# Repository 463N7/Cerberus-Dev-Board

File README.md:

# Cerberus Dev Board

The hardware and programming reference for the Cerberus handheld development board: ESP32-S3 + ESP32-C5, ST7796 display, GT911 touch, microSD, battery monitoring, and expansion interfaces.

**[Open the developer website](https://463n7.github.io/Cerberus-Dev-Board/)** · **[USB firmware installer](https://463n7.github.io/Cerberus-Flasher/)**

This repository documents the device itself, independently of a particular firmware application. **No Cerberus main-device schematics, PCB sources, fabrication files, or netlists are included.** Expansion files have a separate, clearly marked home under [`hardware/expansion/`](hardware/expansion/README.md). The supplied expansion starter includes its connector-only schematic.

**[Expansion starter KiCad project](hardware/expansion/starter/)** · **[Download starter ZIP](https://463n7.github.io/Cerberus-Dev-Board/assets/cerberus-expansion-starter.zip)** — KiCad 10 project, PCB, and expansion connector schematic.

## Developer reference

| Guide | Contents |
| --- | --- |
| [Start here](content/getting-started.md) | Identify the board, install firmware, build, and recover USB |
| [Hardware](content/hardware.md) | Base-board processors, memory, buses, and power devices |
| [Pinouts](content/pinouts.md) | Base-board interfaces, labeled expansion breakout, and six-C5 expansion pinout; RF/NFC map not published during early testing |
| [Expansion add-ons](content/expansion.md) | Six-C5 bank and RF/NFC board; both in testing |
| [Programming](content/programming.md) | Toolchain, source layout, memory setup, protocol, and bring-up |
| [Batteries](content/batteries.md) | Tested batteries, “should fit” candidates, dimensions, polarity, and test evidence |
| [Antennas](content/antennas.md) | Radio-specific antenna requirements, connector checks, and comparison records |
| [Troubleshooting](content/troubleshooting.md) | USB, C5, display, touch, SD, battery, and expansion issues |
| [Downloads](content/downloads.md) | Firmware, reusable pin definitions, examples, and expansion CAD location |
| [Reference and testing](content/revisions.md) | Base-board reference, add-on testing status, and remaining measurements |

Cerberus uses an **S3 N16R2, one onboard C5, and 1-bit SDMMC with a 40 MHz maximum target**. The C5 memory specification uses the smallest standard [C5-WROOM option](https://documentation.espressif.com/esp32-c5-wroom-1_wroom-1u_datasheet_en.html): **N4, 4 MB flash and no PSRAM**. Sentinel's current 2 MB firmware layout is a separate software allocation. The RF/NFC board and six-C5 bank are optional expansion add-ons, both in testing. The expansion breakout table lists all 25 GPIO signals individually, with each processor and side identified as viewed from the labeled face.

## Maintaining the website

Edit the Markdown in `content/`, then generate the static website:

```powershell
python -m pip install -r requirements.txt
python tools/build_site.py
python tools/check_site.py
python -m http.server 8765 --directory docs
```

Open `http://localhost:8765/`. Commit both the Markdown sources and generated `docs/`. GitHub Pages serves `main:/docs`. The repository check verifies generated content, local links, and the boundary excluding main-device design files.

## Compatibility reports

Use the [battery, antenna, or documentation issue templates](https://github.com/463N7/Cerberus-Dev-Board/issues/new/choose). Include exact model numbers, board revision, measurements, test conditions, and photographs that do not reveal device schematics. “Should fit” is a dimensional estimate, not a tested battery recommendation.

No general hardware license is granted by publishing this reference. Expansion CAD and example code will need explicit license notices before broader reuse is advertised. Linked firmware projects retain their own terms.

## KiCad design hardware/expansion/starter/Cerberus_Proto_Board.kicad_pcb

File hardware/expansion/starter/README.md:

# Cerberus expansion starter

An editable starting point for Cerberus expansion boards: four 20-pin header footprints, their connector schematic, and a prototyping area. This is the expansion board project.

## Open the project

Use **KiCad 10.0 or a compatible newer version**. Extract the complete [starter ZIP](https://463n7.github.io/Cerberus-Dev-Board/assets/cerberus-expansion-starter.zip), then open **`Cerberus_Proto_Board.kicad_pro`**. Keep the project, PCB, and schematic together with their matching filenames.

| File | Contents |
| --- | --- |
| `Cerberus_Proto_Board.kicad_pro` | Project and board settings |
| `Cerberus_Proto_Board.kicad_pcb` | Four-layer, 1.6 mm expansion PCB with J1–J4 and an embedded prototyping footprint |
| `Cerberus_Proto_Board.kicad_sch` | Four 20-pin connectors and their signal/power connections |

## Libraries and models

The connectors use standard **2.54 mm, 1 × 20 pin-header footprints**. Symbols are embedded in the schematic. The custom `protoboard` footprint geometry is embedded in the PCB; a separate custom footprint library was not supplied. Save that embedded footprint into your own library before using library-based footprint updates.

Header 3D models reference KiCad 10's standard `${KICAD10_3DMODEL_DIR}` library. Install the standard 3D-model library for those previews. The custom prototyping footprint retains a generic header model, so the 3D view is not a verified mechanical model.

## Using the starter

Check connector references and pin-1 markers against the [Cerberus pinout](https://463n7.github.io/Cerberus-Dev-Board/pinouts.html) when positioning an add-on. Preserve the shared-bus and startup-pin requirements in that reference. Verify net assignments, board clearance, and your changes before fabrication.

These are starter design files. No electrical, mechanical, ERC, or DRC validation report is included. License: not specified in the supplied files.

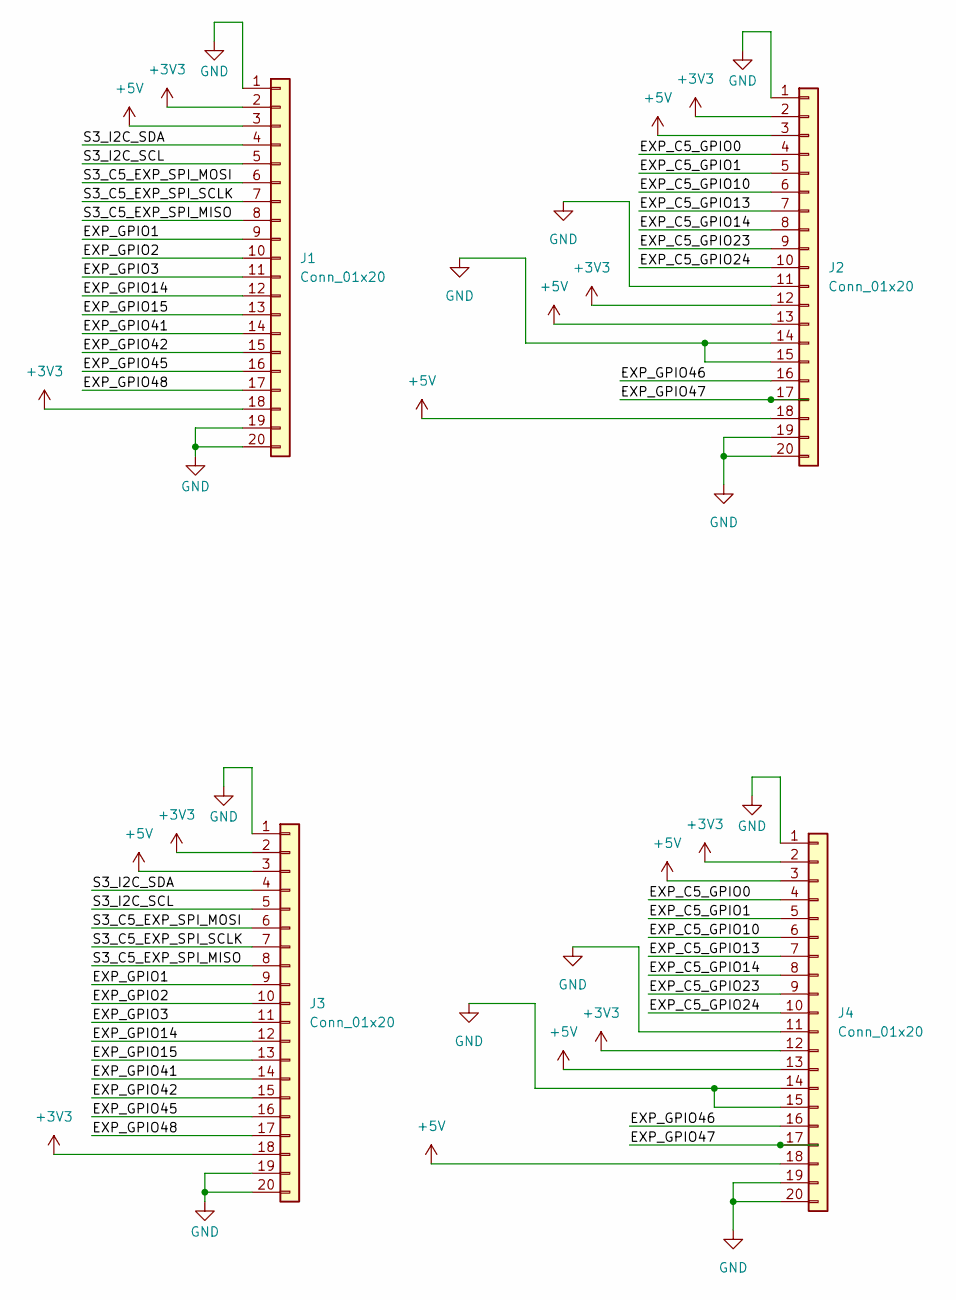
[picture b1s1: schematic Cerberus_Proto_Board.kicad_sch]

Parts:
J1, J2, J3, J4: Conn_01x20; PinHeader_1x20_P2.54mm_Vertical

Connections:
+3V3: J1.2, J1.18, J2.2, J2.12, J3.2, J3.18, J4.2, J4.12
+5V: J1.3, J2.3, J2.13, J2.18, J3.3, J4.3, J4.13, J4.18
/EXP_C5_GPIO0: J2.4, J4.4
/EXP_C5_GPIO1: J2.5, J4.5
/EXP_C5_GPIO10: J2.6, J4.6
/EXP_C5_GPIO13: J2.7, J4.7
/EXP_C5_GPIO14: J2.8, J4.8
/EXP_C5_GPIO23: J2.9, J4.9
/EXP_C5_GPIO24: J2.10, J4.10
/EXP_GPIO1: J1.9, J3.9
/EXP_GPIO2: J1.10, J3.10
/EXP_GPIO3: J1.11, J3.11
/EXP_GPIO14: J1.12, J3.12
/EXP_GPIO15: J1.13, J3.13
/EXP_GPIO41: J1.14, J3.14
/EXP_GPIO42: J1.15, J3.15
/EXP_GPIO45: J1.16, J3.16
/EXP_GPIO46: J2.16, J4.16
/EXP_GPIO47: J2.17, J4.17
/EXP_GPIO48: J1.17, J3.17
/S3_C5_EXP_SPI_MISO: J1.8, J3.8
/S3_C5_EXP_SPI_MOSI: J1.6, J3.6
/S3_C5_EXP_SPI_SCLK: J1.7, J3.7
/S3_I2C_SCL: J1.5, J3.5
/S3_I2C_SDA: J1.4, J3.4
GND: J1.1, J1.19, J1.20, J2.1, J2.11, J2.14, J2.15, J2.19, J2.20, J3.1, J3.19, J3.20, J4.1, J4.11, J4.14, J4.15, J4.19, J4.20

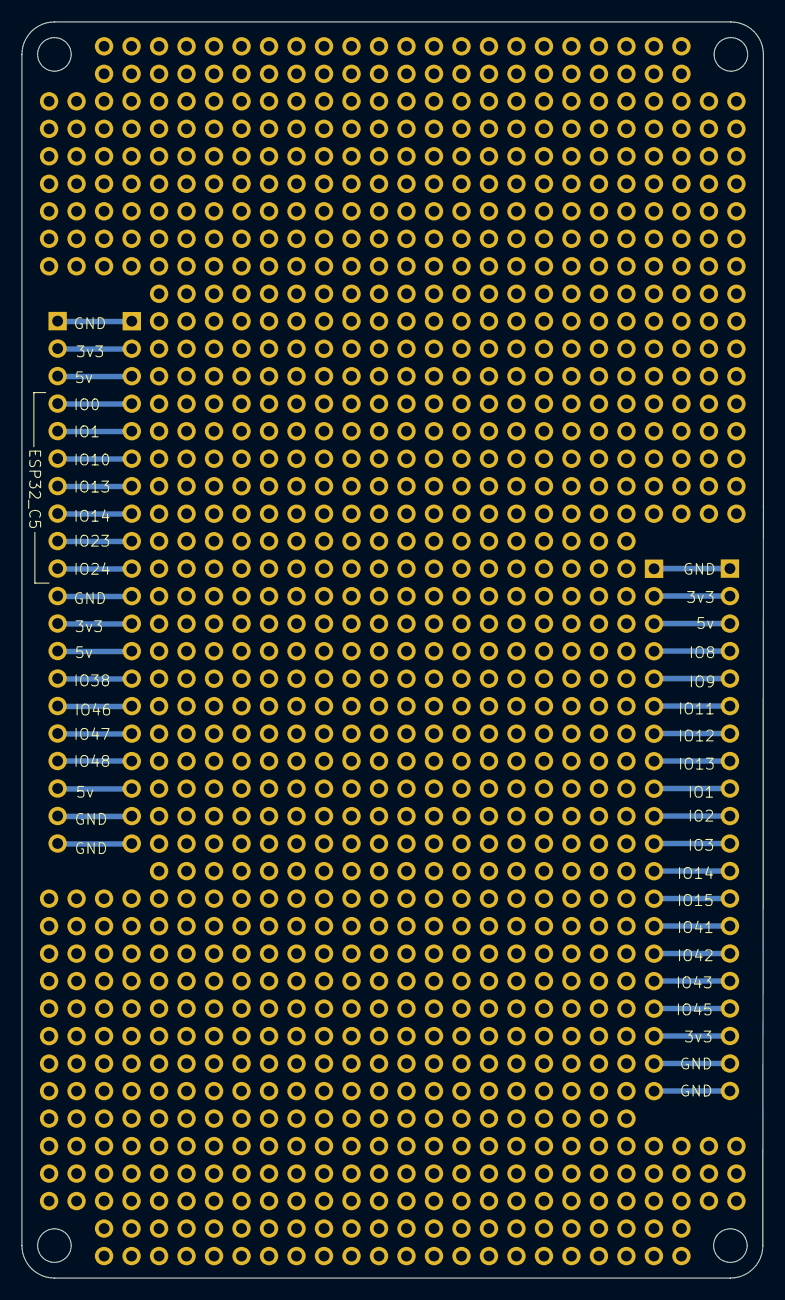
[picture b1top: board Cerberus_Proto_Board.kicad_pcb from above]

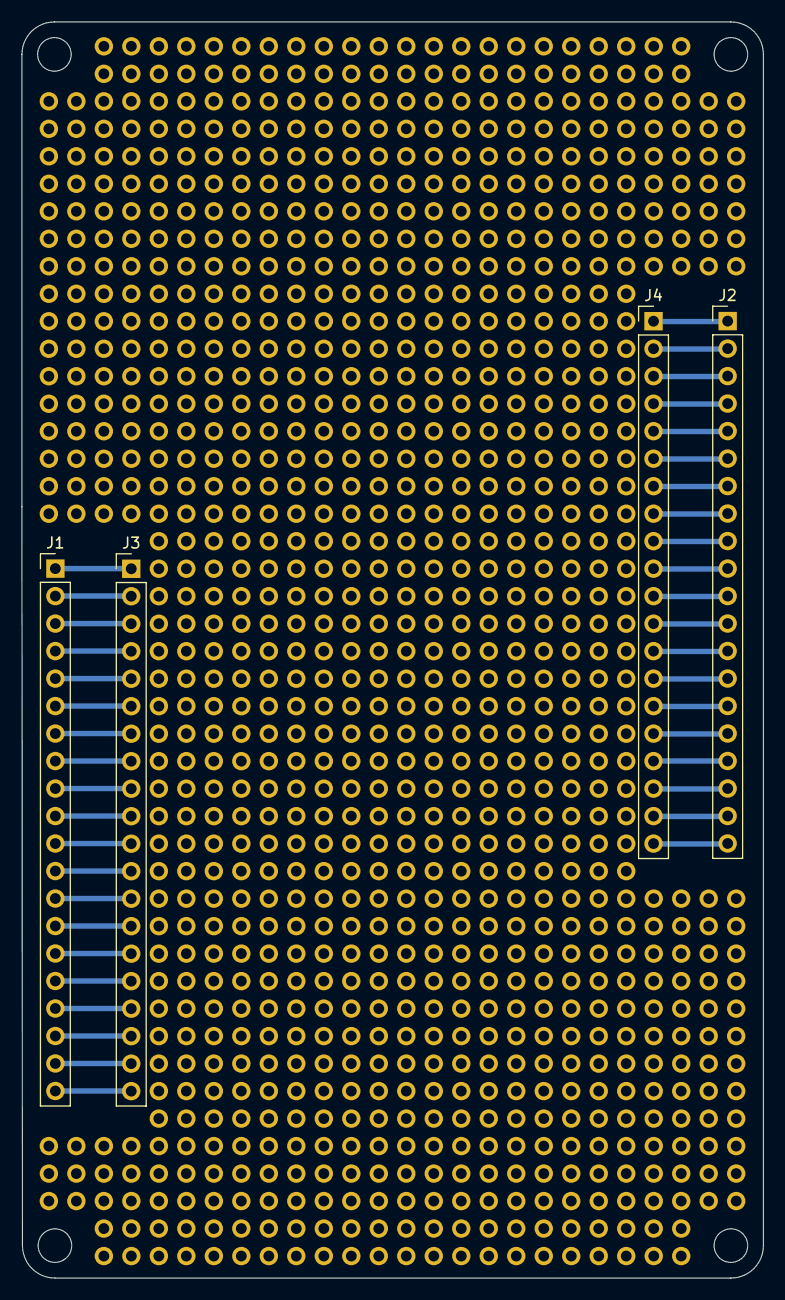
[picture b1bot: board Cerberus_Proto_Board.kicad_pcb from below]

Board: 4 copper layers, 68.5 x 116.1 mm, 4 parts (4 on the bottom side), 26 nets.
